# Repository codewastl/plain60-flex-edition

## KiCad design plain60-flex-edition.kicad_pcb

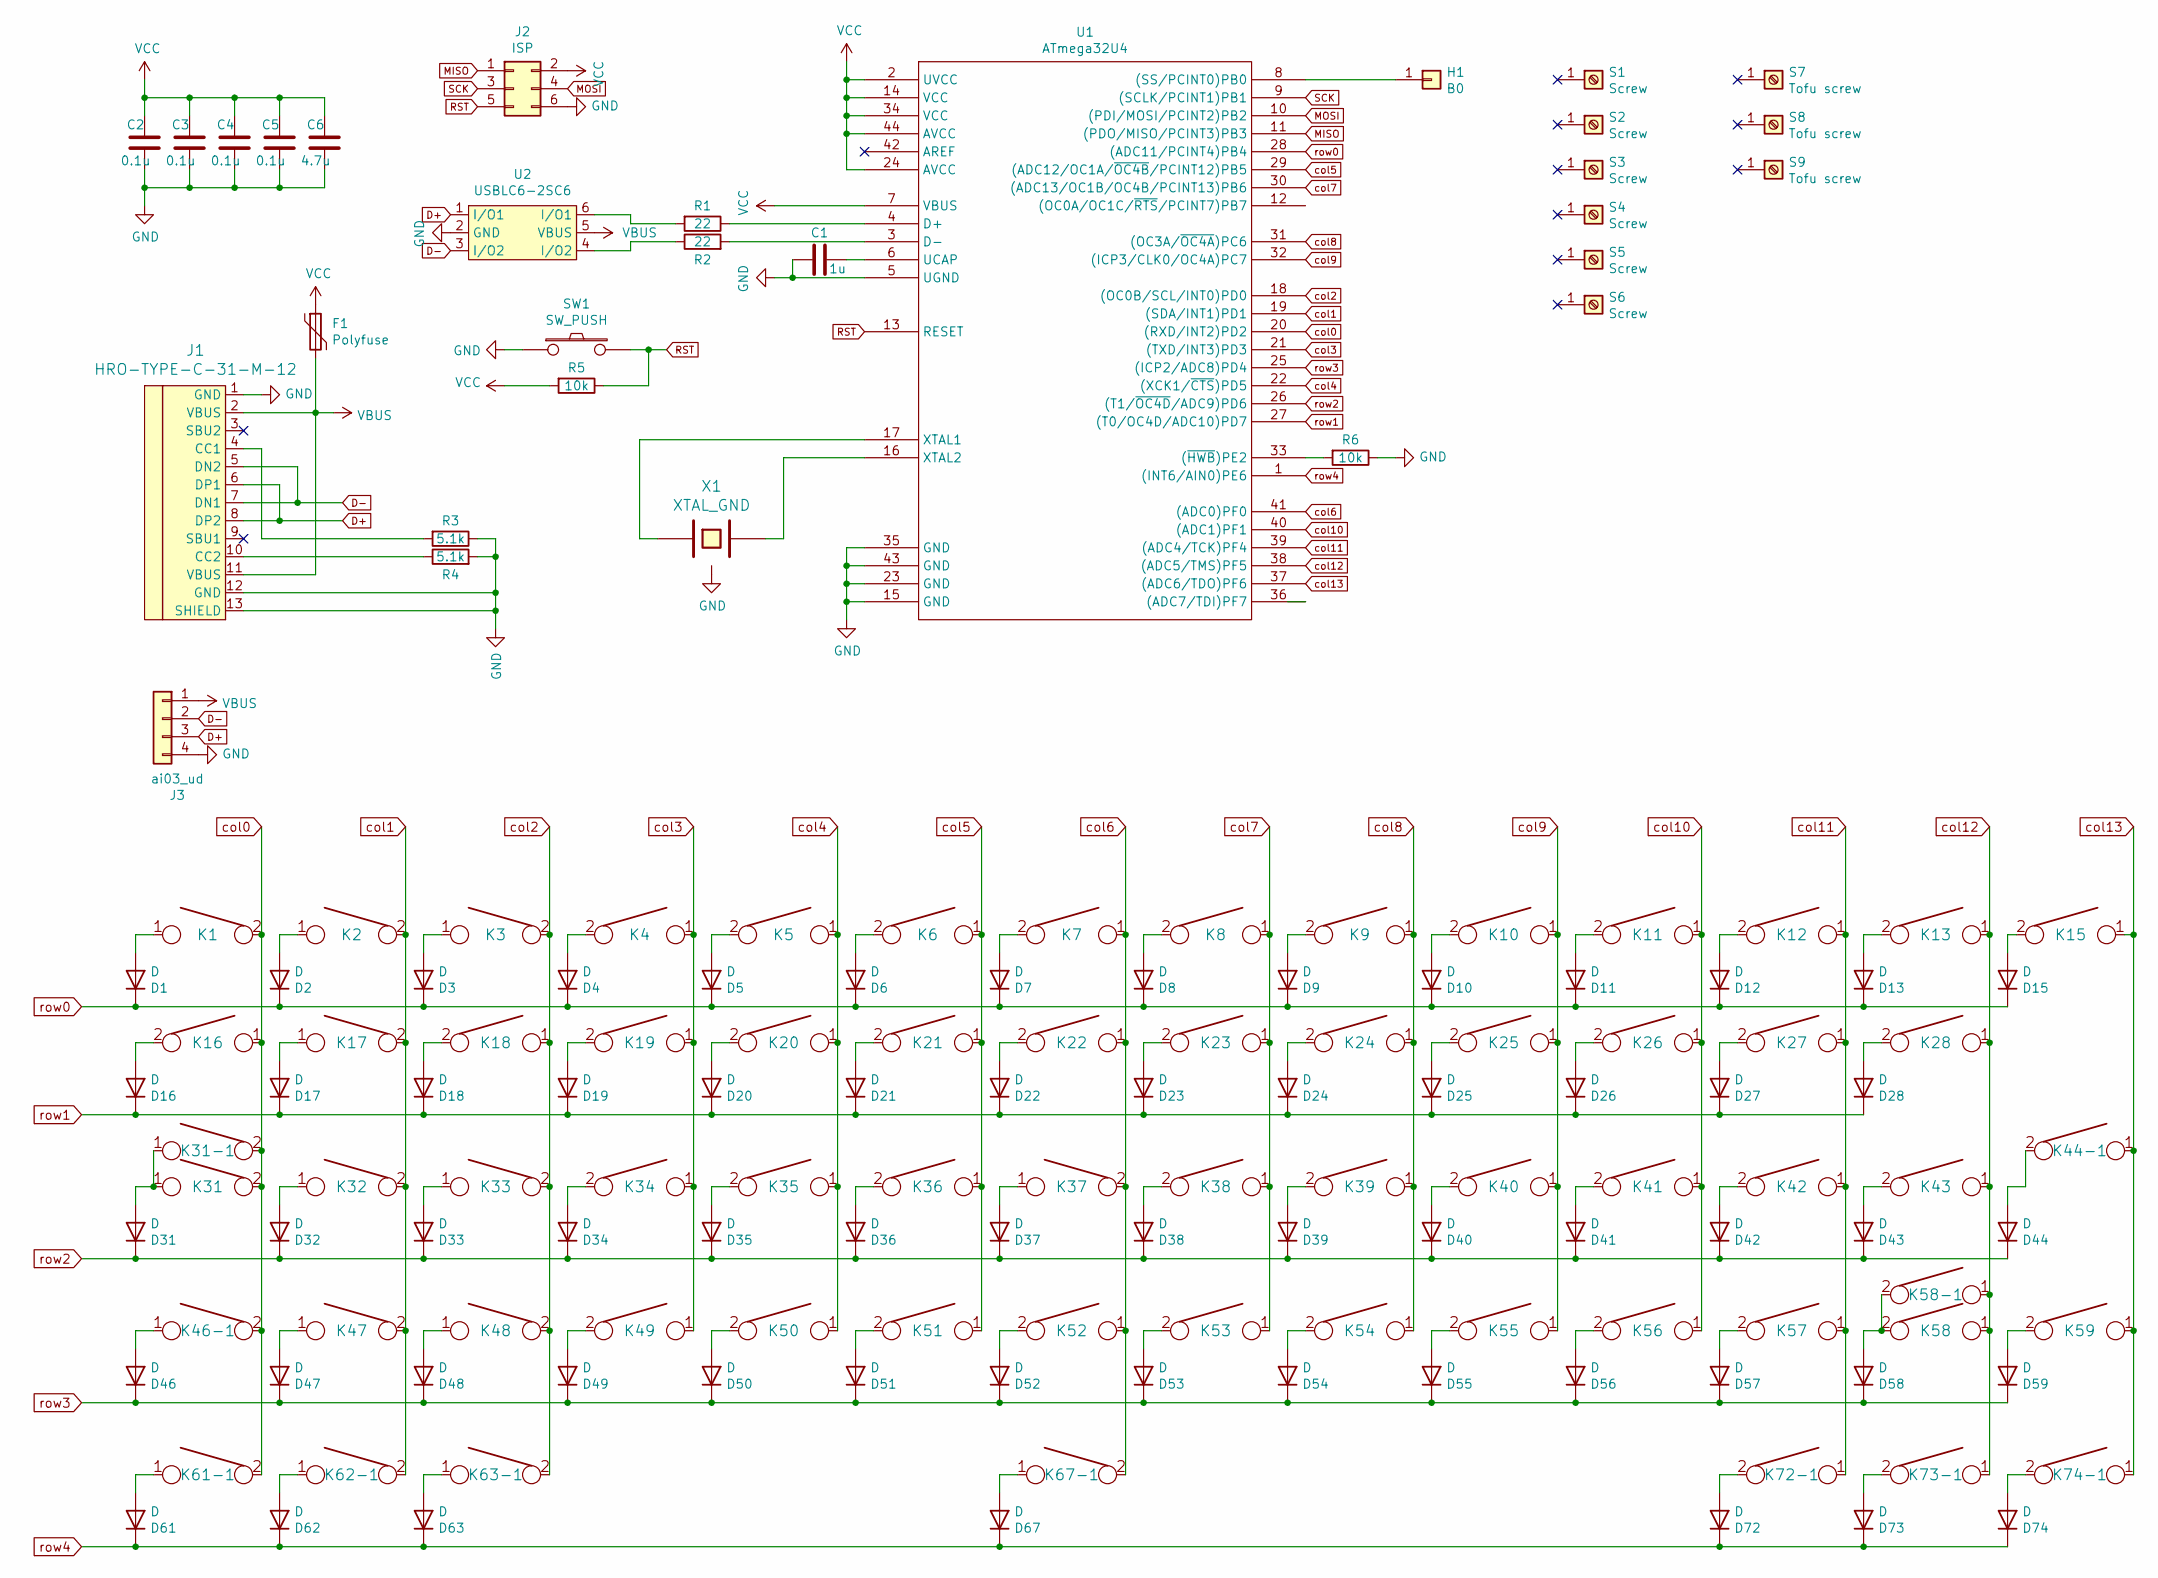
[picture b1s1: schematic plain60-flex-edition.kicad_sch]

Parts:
C1: 1u; C_0805
C2, C3, C4, C5: 0.1u; C_0805
C6: 4.7u; C_0805
D1, D2, D3, D4, D5, D6, D7, D8, D9, D10, D11, D12, D13, D15, D16, D17, D18, D19, D20, D21, D22, D23, D24, D25, D26, D27, D28, D31, D32, D33, D34, D35, D36, D37, D38, D39, D40, D41, D42, D43, D44, D46, D47, D48, D49, D50, D51, D52, D53, D54, D55, D56, D57, D58, D59, D61, D62, D63, D67, D72, D73, D74: D; D_0805
F1: Polyfuse; R_0805
H1: B0; free_pin
J1: HRO-TYPE-C-31-M-12
J2: ISP; isp_standard
J3: ai03_ud; JST_SH_SM04B-SRSS-TB_1x04-1MP_P1.00mm_Horizontal
K1, K2, K3, K4, K5, K6, K7, K8, K9, K10, K11, K12, K13, K17, K18, K19, K20, K21, K22, K23, K24, K25, K26, K27, K28, K32, K33, K34, K35, K36, K37, K38, K39, K40, K41, K42, K43, K47, K48, K49, K50, K51, K52, K53, K54, K55, K56, K57, K59, K62-1, K73-1: KEYSW; CHERRY_PLATE_100H
K15: KEYSW; CHERRY_PCB_200H
K16, K61-1, K63-1, K72-1, K74-1: KEYSW; CHERRY_PLATE_150H
K31, K58-1: KEYSW; CHERRY_PLATE_175H
K31-1, K46-1: KEYSW; CHERRY_PLATE_125H
K44-1: KEYSW; CHERRY_PCB_200H_V
K58: KEYSW; CHERRY_PCB_275H
K67-1: KEYSW; CHERRY_PCB_700H_F
R1, R2: 22; R_0805
R3, R4: 5.1k; R_0805
R5, R6: 10k; R_0805
S1, S2, S3, S6: Screw; 5.5_5x2.5mm
S4, S5: Screw; 10x5_7x2.5mm
S7, S8, S9: Tofu screw; 5.5_5x2.5mm
SW1: SW_PUSH; SW_SPST_TL3342
U1: ATmega32U4; ATMEGA32U4
U2: USBLC6-2SC6; Farnell 1295310
X1: XTAL_GND; Resonator_SMD_muRata_CSTNExxV-3Pin-p1.2

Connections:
D+: J1.6 (DP1), J1.8 (DP2), J3.3, U2.1 (I/O1)
D-: J1.5 (DN2), J1.7 (DN1), J3.2, U2.3 (I/O2)
GND: C1.2, C2.1, C3.1, C4.1, C5.1, C6.1, J1.1 (GND), J1.12 (GND), J1.13 (SHIELD), J2.6, J3.4, R3.1, R4.2, R6.1, SW1.1, U1.5 (UGND), U1.15 (GND), U1.23 (GND), U1.35 (GND), U1.43 (GND), U2.2 (GND), X1.3
MISO: J2.1, U1.11 ((PDO/MISO/PCINT3)PB3)
MOSI: J2.4, U1.10 ((PDI/MOSI/PCINT2)PB2)
unnamed: C1.1, U1.6 (UCAP)
unnamed: D1.2 (A), K1.1
unnamed: D2.2 (A), K2.1
unnamed: D3.2 (A), K3.1
unnamed: D4.2 (A), K4.2
unnamed: D5.2 (A), K5.2
unnamed: D6.2 (A), K6.2
unnamed: D7.2 (A), K7.2
unnamed: D8.2 (A), K8.2
unnamed: D9.2 (A), K9.2
unnamed: D10.2 (A), K10.2
unnamed: D11.2 (A), K11.2
unnamed: D12.2 (A), K12.2
unnamed: D13.2 (A), K13.2
unnamed: D15.2 (A), K15.2
unnamed: D16.2 (A), K16.2
unnamed: D17.2 (A), K17.1
unnamed: D18.2 (A), K18.2
unnamed: D19.2 (A), K19.2
unnamed: D20.2 (A), K20.2
unnamed: D21.2 (A), K21.2
unnamed: D22.2 (A), K22.2
unnamed: D23.2 (A), K23.2
unnamed: D24.2 (A), K24.2
unnamed: D25.2 (A), K25.2
unnamed: D26.2 (A), K26.2
unnamed: D27.2 (A), K27.2
unnamed: D28.2 (A), K28.2
unnamed: D31.2 (A), K31.1, K31-1.1
unnamed: D32.2 (A), K32.1
unnamed: D33.2 (A), K33.1
unnamed: D34.2 (A), K34.2
unnamed: D35.2 (A), K35.2
unnamed: D36.2 (A), K36.2
unnamed: D37.2 (A), K37.1
unnamed: D38.2 (A), K38.2
unnamed: D39.2 (A), K39.2
unnamed: D40.2 (A), K40.2
unnamed: D41.2 (A), K41.2
unnamed: D42.2 (A), K42.2
unnamed: D43.2 (A), K43.2
unnamed: D44.2 (A), K44-1.2
unnamed: D46.2 (A), K46-1.1
unnamed: D47.2 (A), K47.1
unnamed: D48.2 (A), K48.1
unnamed: D49.2 (A), K49.2
unnamed: D50.2 (A), K50.2
unnamed: D51.2 (A), K51.2
unnamed: D52.2 (A), K52.2
unnamed: D53.2 (A), K53.2
unnamed: D54.2 (A), K54.2
unnamed: D55.2 (A), K55.2
unnamed: D56.2 (A), K56.2
unnamed: D57.2 (A), K57.2
unnamed: D58.2 (A), K58.2, K58-1.2
unnamed: D59.2 (A), K59.2
unnamed: D61.2 (A), K61-1.1
unnamed: D62.2 (A), K62-1.1
unnamed: D63.2 (A), K63-1.1
unnamed: D67.2 (A), K67-1.1
unnamed: D72.2 (A), K72-1.2
unnamed: D73.2 (A), K73-1.2
unnamed: D74.2 (A), K74-1.2
unnamed: H1.1, U1.8 ((SS/PCINT0)PB0)
unnamed: J1.4 (CC1), R3.2
unnamed: J1.10 (CC2), R4.1
unnamed: R1.1, U1.4 (D+)
unnamed: R1.2, U2.6 (I/O1)
unnamed: R2.1, U2.4 (I/O2)
unnamed: R2.2, U1.3 (D-)
unnamed: R6.2, U1.33 ((~HWB~)PE2)
unnamed: U1.16 (XTAL2), X1.2
unnamed: U1.17 (XTAL1), X1.1
RST: J2.5, R5.1, SW1.2, U1.13 (RESET)
SCK: J2.3, U1.9 ((SCLK/PCINT1)PB1)
VBUS: F1.2, J1.2 (VBUS), J1.11 (VBUS), J3.1, U2.5 (VBUS)
VCC: C2.2, C3.2, C4.2, C5.2, C6.2, F1.1, J2.2, R5.2, U1.2 (UVCC), U1.7 (VBUS), U1.14 (VCC), U1.24 (AVCC), U1.34 (VCC), U1.44 (AVCC)
col0: K1.2, K16.1, K31.2, K31-1.2, K46-1.2, K61-1.2, U1.20 ((RXD/INT2)PD2)
col1: K2.2, K17.2, K32.2, K47.2, K62-1.2, U1.19 ((SDA/INT1)PD1)
col2: K3.2, K18.1, K33.2, K48.2, K63-1.2, U1.18 ((OC0B/SCL/INT0)PD0)
col3: K4.1, K19.1, K34.1, K49.1, U1.21 ((TXD/INT3)PD3)
col4: K5.1, K20.1, K35.1, K50.1, U1.22 ((XCK1/~CTS~)PD5)
col5: K6.1, K21.1, K36.1, K51.1, U1.29 ((ADC12/OC1A/~OC4B~/PCINT12)PB5)
col6: K7.1, K22.1, K37.2, K52.1, K67-1.2, U1.41 ((ADC0)PF0)
col7: K8.1, K23.1, K38.1, K53.1, U1.30 ((ADC13/OC1B/OC4B/PCINT13)PB6)
col8: K9.1, K24.1, K39.1, K54.1, U1.31 ((OC3A/~OC4A~)PC6)
col9: K10.1, K25.1, K40.1, K55.1, U1.32 ((ICP3/CLK0/OC4A)PC7)
col10: K11.1, K26.1, K41.1, K56.1, U1.40 ((ADC1)PF1)
col11: K12.1, K27.1, K42.1, K57.1, K72-1.1, U1.39 ((ADC4/TCK)PF4)
col12: K13.1, K28.1, K43.1, K58.1, K58-1.1, K73-1.1, U1.38 ((ADC5/TMS)PF5)
col13: K15.1, K44-1.1, K59.1, K74-1.1, U1.37 ((ADC6/TDO)PF6)
col14: U1.36 ((ADC7/TDI)PF7)
row0: D1.1 (K), D2.1 (K), D3.1 (K), D4.1 (K), D5.1 (K), D6.1 (K), D7.1 (K), D8.1 (K), D9.1 (K), D10.1 (K), D11.1 (K), D12.1 (K), D13.1 (K), D15.1 (K), U1.28 ((ADC11/PCINT4)PB4)
row1: D16.1 (K), D17.1 (K), D18.1 (K), D19.1 (K), D20.1 (K), D21.1 (K), D22.1 (K), D23.1 (K), D24.1 (K), D25.1 (K), D26.1 (K), D27.1 (K), D28.1 (K), U1.27 ((T0/OC4D/ADC10)PD7)
row2: D31.1 (K), D32.1 (K), D33.1 (K), D34.1 (K), D35.1 (K), D36.1 (K), D37.1 (K), D38.1 (K), D39.1 (K), D40.1 (K), D41.1 (K), D42.1 (K), D43.1 (K), D44.1 (K), U1.26 ((T1/~OC4D~/ADC9)PD6)
row3: D46.1 (K), D47.1 (K), D48.1 (K), D49.1 (K), D50.1 (K), D51.1 (K), D52.1 (K), D53.1 (K), D54.1 (K), D55.1 (K), D56.1 (K), D57.1 (K), D58.1 (K), D59.1 (K), U1.25 ((ICP2/ADC8)PD4)
row4: D61.1 (K), D62.1 (K), D63.1 (K), D67.1 (K), D72.1 (K), D73.1 (K), D74.1 (K), U1.1 ((INT6/AIN0)PE6)

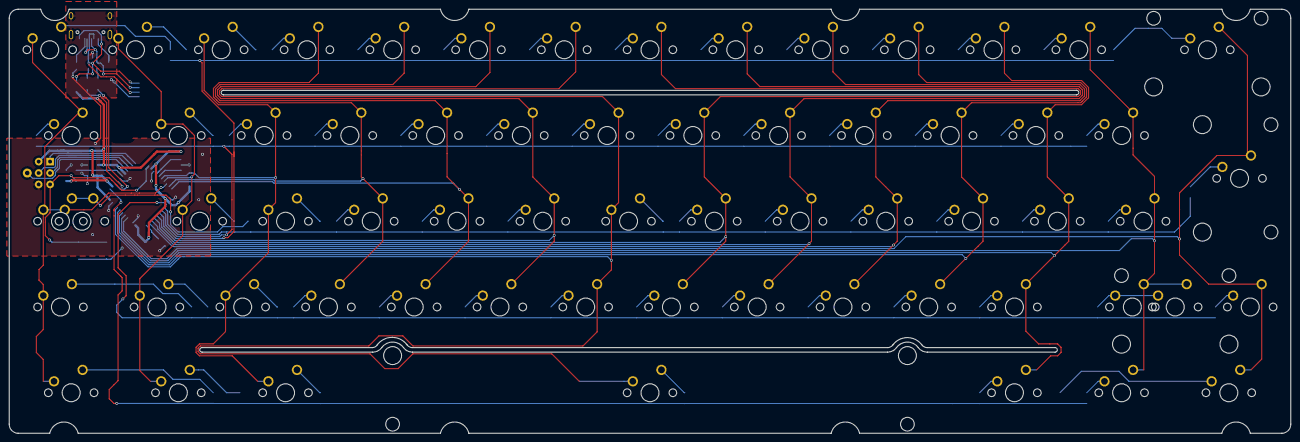
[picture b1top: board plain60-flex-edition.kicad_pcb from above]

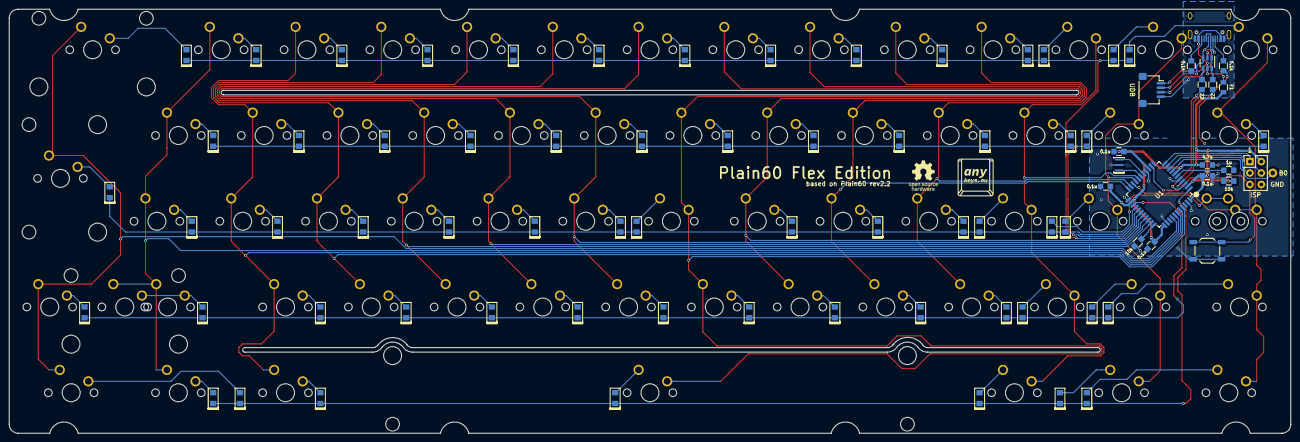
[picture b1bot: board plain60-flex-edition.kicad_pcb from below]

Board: 2 copper layers, 284.7 x 94.2 mm, 156 parts (83 on the bottom side), 101 nets.

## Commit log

2022-02-12 removed ansi and 6.25u support
